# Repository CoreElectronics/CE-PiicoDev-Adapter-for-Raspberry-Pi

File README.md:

# PiicoDev® Adapter for Raspberry Pi

*This is the hardware repo for the [PiicoDev® Adapter for Raspberry Pi](https://core-electronics.com.au/catalog/product/view/sku/CE07690)*

The PiicoDev® Adapter for Raspberry Pi is a great way to connect sensors to your Raspberry Pi. Use the on-board PiicoDev connectors to quickly and easily connect with the [PiicoDev](https://core-electronics.com.au/piicodev) family of sensor modules without soldering.

**Features**

- Rapid prototyping with solderless connections
- Other useful pins are broken out
- PiicoDev connector, compatible with Qwiic and STEMMA QT (3.3V only)
- Manufactured and [supported](https://core-electronics.com.au/contacts/) in Australia by Core Electronics

**Technical Details**

- Dimensions: 22x51mm
- PiicoDev connector pinout:
  -1 GND
  -2 3.3V
  -3 SDA
  -4 SCL
- The I2C Bus presented at the PiicoDev connector contains series 120Ohm resistances to prevent destructive signal undershoot. Refer to the schematic for more information. To operate without these series resistors, users may connect directly to the GPIO instead.

# License
This project is open source - please review the LICENSE.md file for further licensing information.

If you have any technical questions, or concerns about licensing, please contact technical support on the [Core Electronics forums](https://forum.core-electronics.com.au/).

---
*\"PiicoDev" is a registered trademark of Core Electronics Pty Ltd*

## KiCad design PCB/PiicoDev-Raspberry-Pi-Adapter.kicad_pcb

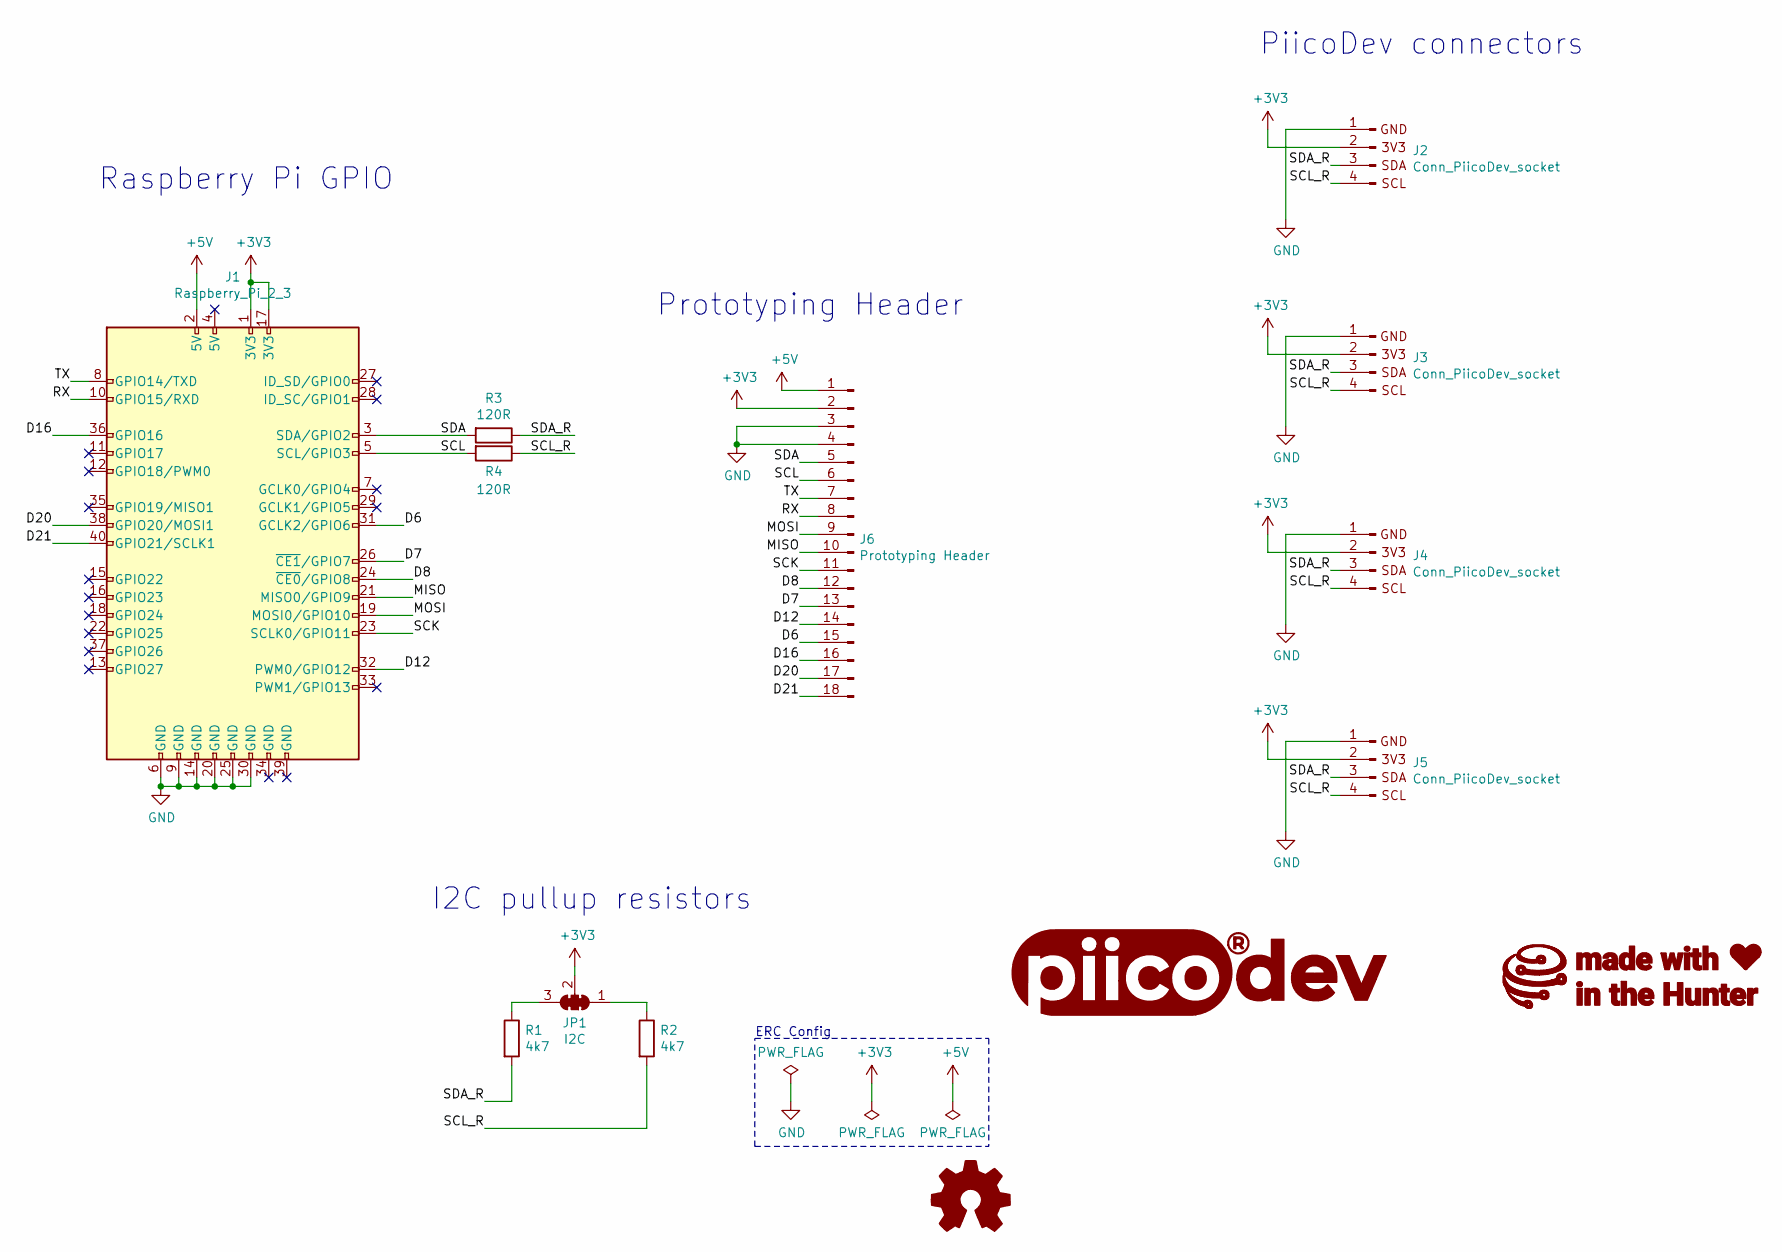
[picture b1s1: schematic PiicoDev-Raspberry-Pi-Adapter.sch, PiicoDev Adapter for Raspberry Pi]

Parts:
G1: LOGO_PiicoDev; piicodev_logo_10.2x2.5mm
G2: LOGO_CoreElectronics_made-with-love; piicodev_logo_10.2x2.5mm
J1: Raspberry_Pi_2_3; PinSocket_2x20_P2.54mm_Vertical_SMD_With_Post
J2, J3, J4, J5: Conn_PiicoDev_socket; JST_SH_SM04B-SRSS-TB_1x04-1MP_P1.00mm_Horizontal
J6: Prototyping Header; PinHeader_1x18_P2.54mm_Vertical
JP1: I2C; SolderJumper-3_P1.3mm_Closed_RoundedPad1.0x1.5mm_NumberLabe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
LOGO1: Logo_Open_Hardware_Small; oshw_3.9x3.5mm
R1, R2: 4k7; R_0402_1005Metric
R3, R4: 120R; R_0402_1005Metric

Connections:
+3V3: J1.1 (3V3), J1.17 (3V3), J2.2, J3.2, J4.2, J5.2, J6.2, JP1.2 (C)
+5V: J1.2 (5V), J6.1
/D6: J1.31 (GCLK2/GPIO6), J6.15
/D7: J1.26 (~CE1~/GPIO7), J6.13
/D8: J1.24 (~CE0~/GPIO8), J6.12
/D12: J1.32 (PWM0/GPIO12), J6.14
/D16: J1.36 (GPIO16), J6.16
/D20: J1.38 (GPIO20/MOSI1), J6.17
/D21: J1.40 (GPIO21/SCLK1), J6.18
/MISO: J1.21 (MISO0/GPIO9), J6.10
/MOSI: J1.19 (MOSI0/GPIO10), J6.9
/RX: J1.10 (GPIO15/RXD), J6.8
/SCK: J1.23 (SCLK0/GPIO11), J6.11
/SCL: J1.5 (SCL/GPIO3), J6.6, R4.2
/SCL_R: J2.4, J3.4, J4.4, J5.4, R2.2, R4.1
/SDA: J1.3 (SDA/GPIO2), J6.5, R3.2
/SDA_R: J2.3, J3.3, J4.3, J5.3, R1.2, R3.1
/TX: J1.8 (GPIO14/TXD), J6.7
GND: J1.6 (GND), J1.9 (GND), J1.14 (GND), J1.20 (GND), J1.25 (GND), J1.30 (GND), J2.1, J3.1, J4.1, J5.1, J6.3, J6.4
unnamed: JP1.1 (A), R2.1
unnamed: JP1.3 (B), R1.1

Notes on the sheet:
Prototyping Header
PiicoDev connectors
Raspberry Pi GPIO
I2C pullup resistors
ERC Config

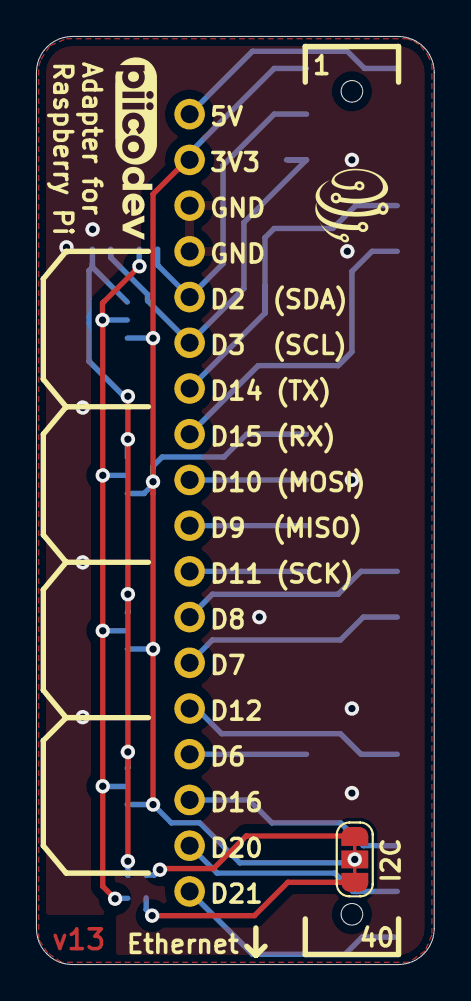
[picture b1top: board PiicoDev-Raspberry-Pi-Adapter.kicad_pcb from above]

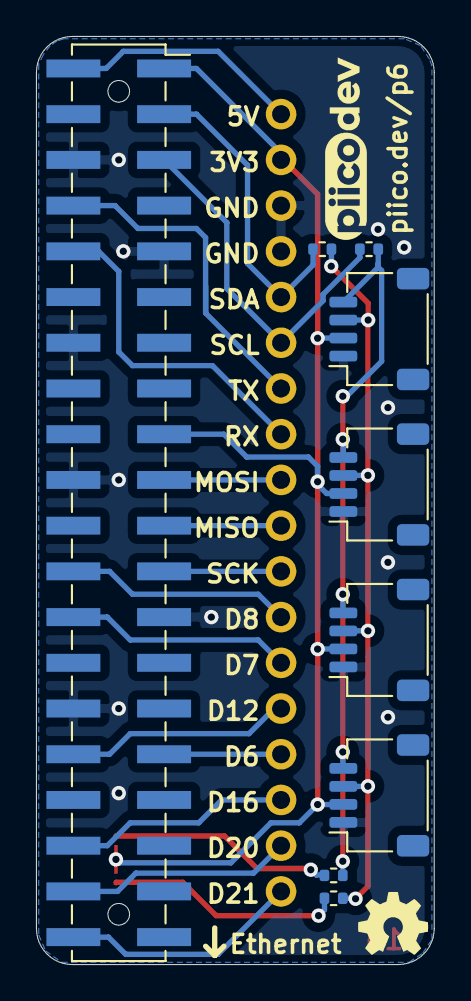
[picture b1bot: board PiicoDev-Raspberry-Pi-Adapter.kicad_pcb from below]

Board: 2 copper layers, 22.1 x 51.6 mm, 14 parts (11 on the bottom side), 21 nets.

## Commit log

2021-04-16 Add Logo to silkscreen
2021-06-28 Bump to v11 - update header footprint to include post-holes
2021-10-29 Add 120R to SCL & SDA. Improve silk screen.
2022-01-18 v13
    Add Raspberry Pi connector pin numbers to silk screen
    Update solder jumper with thinner cut trace
    Fix PiicoDev connector ground connection
2022-01-18 Change date
2022-02-24 update pdf to v13

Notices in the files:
PCB/PiicoDev-Raspberry-Pi-Adapter.kicad_pcb:
Creative Commons Share-alike 4.0 International
PCB/PiicoDev-Raspberry-Pi-Adapter.sch:
http://creativecommons.org/licenses/by-sa/4.0
